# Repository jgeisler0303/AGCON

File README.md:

# This Project is no longer maintained. Please see if this might be an alternative for you: https://github.com/jgeisler0303/CANFestivino

Introduction
============
This project aims to provide hardware and software to build a versatile and generic device that can be used to connect all sorts of sensors and actuators to a CANopen network. My main intention is to use these devices in home automation applications.

Originally I wanted to cal the project CANduino but that name is already taken. Now I think that AGCON -- Arduino Generic CANopen Node -- is much more descriptive and unique.

The hardware is based on the ubiquitous ATmega 328 microcontroller found e.g. on the Arduino Uno. The mc is preflashed with the Arduino bootloader and can be programmed using an FTDI USB to serial adapter.

Connection to the CAN bus is established via an MCP2515 CAN controller.

The free input and output pins of the ATmega are not routed to the available connectors. Instead, the board features a prototyping area that can be used to customize the device to connect to any sensor or actuator. This allows to mass-produce the board and use it for many different applications.

The software is currently based on the http://www.canfestival.org/ CANopen stack adapted to run on the ATmega 328. For sending and receiving of CAN messages a modified version of the https://github.com/Seeed-Studio/CAN_BUS_Shield library is used. This example code is configured to let the user read 6 digital inputs and write 4 digital outputs. The software has to be compiled using the avr-gcc via a makefile.

The CANopen stack is a protocol that runs ontop of the CAN communication layer and facilitates the acces to device parameters and input/ouput data in a standardized way. Check out the following links to get a quick start on the basic concept:

* http://en.wikipedia.org/wiki/CANopen
* http://www.canopensolutions.com/english/about_canopen/about_canopen.shtml
* http://www.can-cia.org/index.php?id=503

In the future I plan to rewrite the software as an Arduino library so that the Arduino IDE can be used to configure the device behaviour, e.g. read special sensor protocols or to control pwm outputs.

Getting Started
===============
To compile the software, got to the Software/CanFestival/examples/Arduino subfolder and run ```make```. (This is assuming you have the avr-gcc compiler installed). If you have a USB to serial adapter connected to your PC and board you can also run ```make flash``` to directly download the new programm to your controller.
The software is not restricted to run on the supplied controller board. Though I haye not tested it, the software can be run on most Arduino boards with a CAN bus shield. But beware that in its current incarnation the SPI chip selection of the MCP2515 is not connected to PB2 (Arduino pin 10). If you want to use the software with CAN bus shields you will probably have to change the following line in mcp_can.c to match your chip select configuration:
```c
#define DDR_CS DDRD
#define PORT_CS PORTD
#define P_CS PD7
```

For the standard SS pin you will have to change these to
```c
#define DDR_CS DDRB
#define PORT_CS PORTB
#define P_CS PB2
```

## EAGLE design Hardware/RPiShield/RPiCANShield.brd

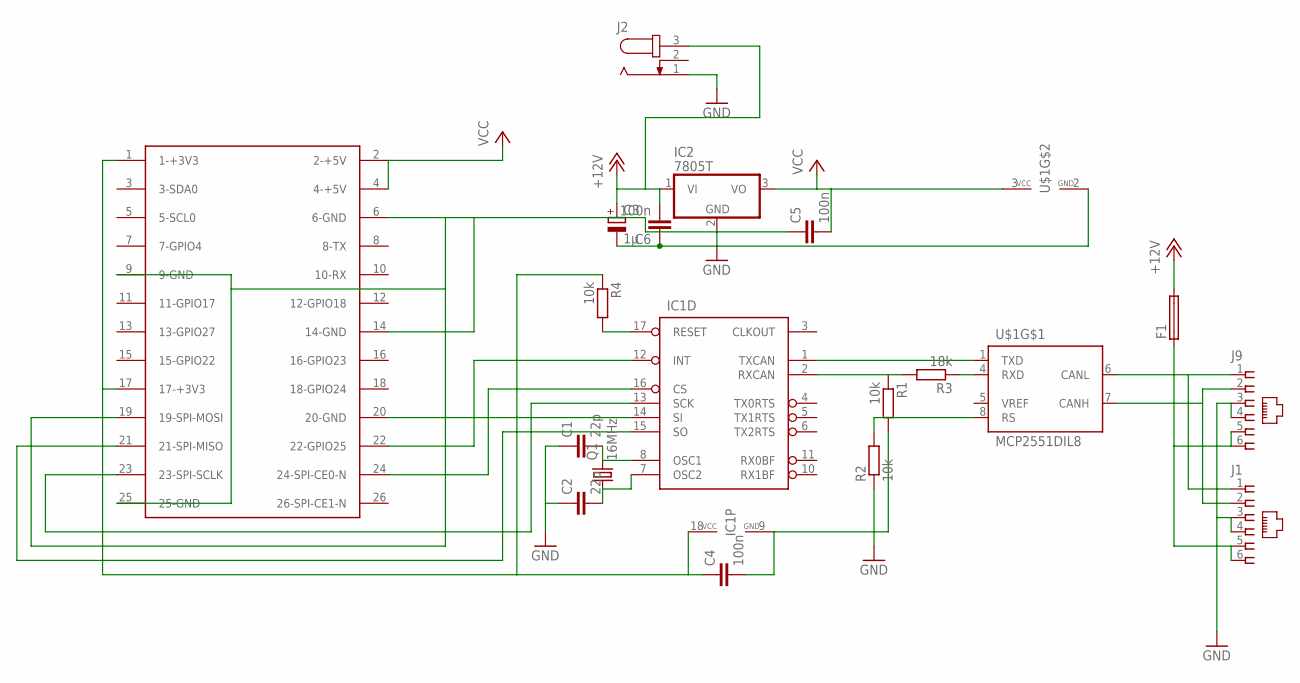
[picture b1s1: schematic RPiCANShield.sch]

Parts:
C1, C2: 22p; C025-024X044
C3: 1µ; E2-5
C4, C5, C6: 100n; C050-024X044
F1: PICOFUSE
IC1: MCP2515P; DIL18
IC2: 7805T; TO220H
J1, J9: 520250-3
J2: JACK-PLUG0; SPC4077
Q1: 16MHz; HC18U-V
R1, R2: 10k; 0207/7
R3: 18k; 0207/7
R4: 10k; 0204/5
U$1: MCP2551DIL8; DIL08
U$2: RASPBERRY-PI

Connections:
+12V: C3.+, C6.2, F1.2, IC2.1 (VI), J2.3
GND: C1.1, C2.1, C3.-, C4.2, C5.1, C6.1, IC1.9 (GND), IC2.2 (GND), J1.3, J1.4, J2.1, J9.3, J9.4, R1.2, R2.1, U$1.2 (GND), U$2.6 (6-GND), U$2.9 (9-GND), U$2.14 (14-GND), U$2.20 (20-GND), U$2.25 (25-GND)
unnamed: IC1.1 (TXCAN), U$1.1 (TXD)
unnamed: R3.1, U$1.4 (RXD)
unnamed: J1.1, J9.1, U$1.6 (CANL)
unnamed: J1.2, J9.2, U$1.7 (CANH)
unnamed: F1.1, J1.5, J1.6, J9.5, J9.6
unnamed: IC1.2 (RXCAN), R1.1, R3.2
unnamed: R2.2, U$1.8 (RS)
unnamed: C4.1, IC1.18 (VCC), R4.1, U$2.1 (1-+3V3), U$2.17 (17-+3V3)
unnamed: IC1.17 (RESET), R4.2
unnamed: IC1.16 (CS), U$2.24 (24-SPI-CE0-N)
unnamed: IC1.13 (SCK), U$2.23 (23-SPI-SCLK)
unnamed: IC1.14 (SI), U$2.19 (19-SPI-MOSI)
unnamed: IC1.12 (INT), U$2.22 (22-GPIO25)
unnamed: IC1.15 (SO), U$2.21 (21-SPI-MISO)
unnamed: C1.2, IC1.8 (OSC1), Q1.2
unnamed: C2.2, IC1.7 (OSC2), Q1.1
VCC: C5.2, IC2.3 (VO), U$1.3 (VCC), U$2.2 (2-+5V), U$2.4 (4-+5V)

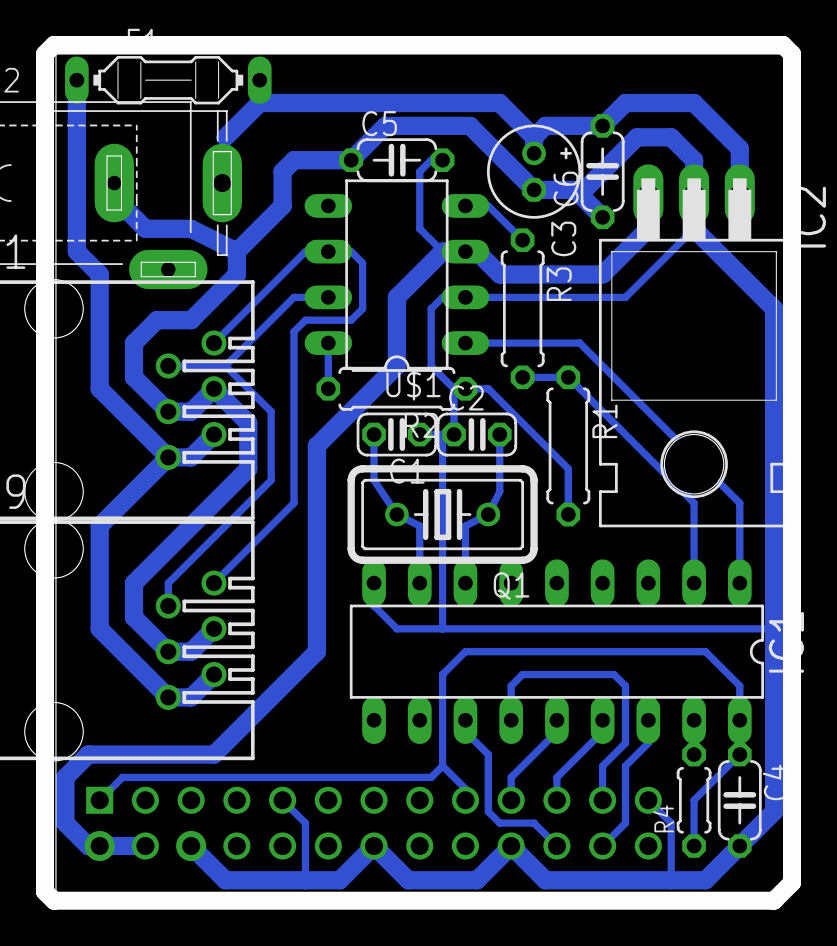
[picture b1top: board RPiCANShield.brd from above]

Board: 2 copper layers, 41.5 x 47.5 mm, 19 parts (1 on the bottom side), 19 nets.

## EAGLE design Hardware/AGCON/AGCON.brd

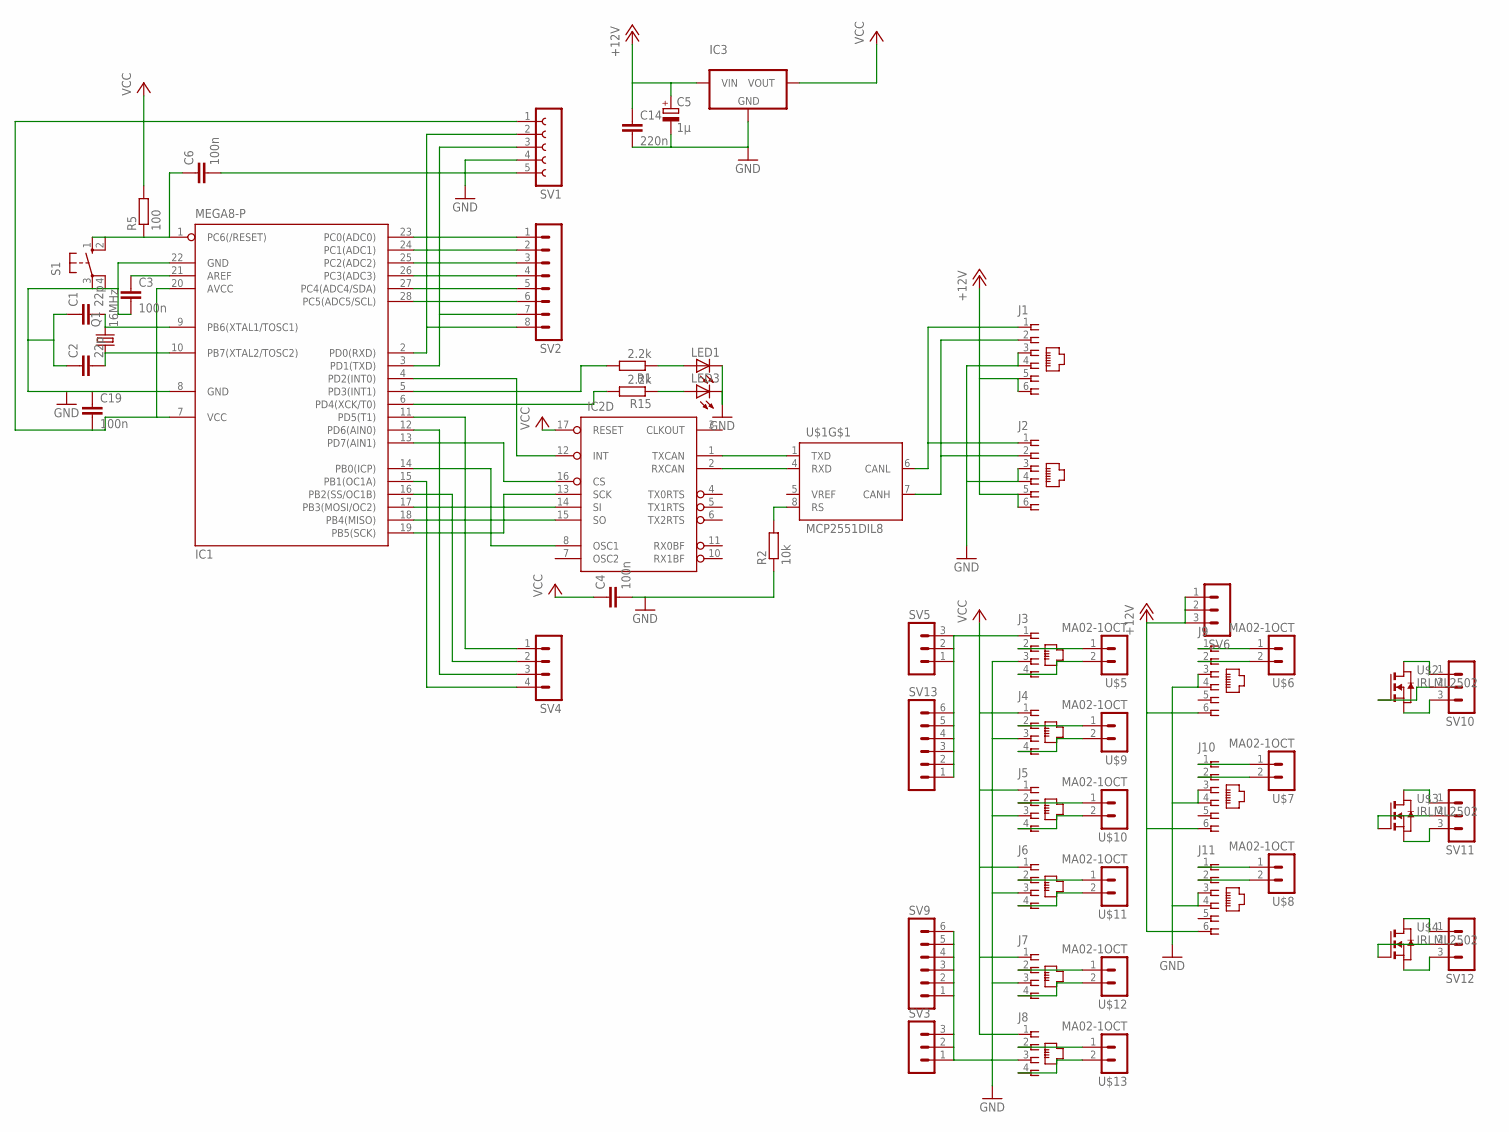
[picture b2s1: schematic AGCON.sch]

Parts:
C1, C2: 22p; C025-024X044
C3, C4, C6, C19: 100n; C050-024X044
C5: 1µ; E5-10,5
C14: 220n; C050-024X044
IC1: MEGA8-P; DIL28-3
IC2: MCP2515P; DIL18
IC3: MCP1702; TO-92
J1, J2, J9, J10, J11: 520250-3
J3, J4, J5, J6, J7, J8: 520249-2
LED1, LED3: LED3MM
Q1: 16MHz; HC18U-V
R1, R15: 2.2k; 0207/7
R2: 10k; 0207/7
R5: 100; 0207/7
S1: 10-XX; B3F-10XX
SV1: FE05-1
SV2: MA08-1OCT
SV3, SV5, SV6, SV10, SV11, SV12: MA03-1OCT
SV4: MA04-1OCT
SV9, SV13: MA06-1MA06-1OCT; MA06-1OCT
U$1: MCP2551DIL8; DIL08
U$2, U$3, U$4: IRLML2502; SOT-23
U$5, U$6, U$7, U$8, U$9, U$10, U$11, U$12, U$13: MA02-1OCT

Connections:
+12V: C5.+, C14.1, IC3.2 (VIN), J1.5, J1.6, J2.5, J2.6, J9.6, J10.6, J11.6, SV6.1, SV6.2, SV6.3
GND: C1.1, C2.1, C3.2, C4.2, C5.-, C14.2, C19.1, IC1.8 (GND), IC1.22 (GND), IC2.9 (GND), IC3.1 (GND), J1.3, J1.4, J2.3, J2.4, J3.3, J4.3, J5.3, J6.3, J7.3, J8.3, J9.3, J9.4, J10.3, J10.4, J11.3, J11.4, LED1.K (C), LED3.K (C), R2.1, S1.3, S1.4 (P1), SV1.4, SV3.1, SV3.2, SV3.3, SV9.1, SV9.2, SV9.3, SV9.4, SV9.5, SV9.6, U$1.2 (GND)
unnamed: IC1.18 (PB4(MISO)), IC2.15 (SO)
unnamed: IC1.17 (PB3(MOSI/OC2)), IC2.14 (SI)
unnamed: IC1.19 (PB5(SCK)), IC2.13 (SCK)
unnamed: IC2.1 (TXCAN), U$1.1 (TXD)
unnamed: IC2.2 (RXCAN), U$1.4 (RXD)
unnamed: J1.1, J2.1, U$1.6 (CANL)
unnamed: J1.2, J2.2, U$1.7 (CANH)
unnamed: IC1.6 (PD4(XCK/T0)), R15.2
unnamed: C6.1, IC1.1 (PC6(/RESET)), R5.1, S1.1 (S), S1.2 (S1)
unnamed: LED1.A, R1.1
unnamed: C6.2, SV1.5
unnamed: LED3.A, R15.1
unnamed: IC1.5 (PD3(INT1)), R1.2
unnamed: IC1.14 (PB0(ICP)), IC2.8 (OSC1)
unnamed: R2.2, U$1.8 (RS)
unnamed: IC1.3 (PD1(TXD)), SV1.3, SV2.7
unnamed: IC1.2 (PD0(RXD)), SV1.2, SV2.8
unnamed: IC1.4 (PD2(INT0)), IC2.12 (INT)
unnamed: IC1.13 (PD7(AIN1)), IC2.16 (CS)
unnamed: C3.1, IC1.21 (AREF)
unnamed: IC1.23 (PC0(ADC0)), SV2.1
unnamed: C1.2, IC1.9 (PB6(XTAL1/TOSC1)), Q1.2
unnamed: C2.2, IC1.10 (PB7(XTAL2/TOSC2)), Q1.1
unnamed: IC1.24 (PC1(ADC1)), SV2.2
unnamed: IC1.25 (PC2(ADC2)), SV2.3
unnamed: IC1.26 (PC3(ADC3)), SV2.4
unnamed: IC1.27 (PC4(ADC4/SDA)), SV2.5
unnamed: IC1.28 (PC5(ADC5/SCL)), SV2.6
unnamed: J4.2, U$9.1
unnamed: J5.2, U$10.1
unnamed: IC1.11 (PD5(T1)), SV4.1
unnamed: IC1.12 (PD6(AIN0)), SV4.3
unnamed: IC1.15 (PB1(OC1A)), SV4.4
unnamed: IC1.16 (PB2(SS/OC1B)), SV4.2
unnamed: J6.2, U$11.1
unnamed: J9.1, U$6.1
unnamed: J9.2, U$6.2
unnamed: J10.1, U$7.1
unnamed: J3.2, U$5.1
unnamed: J3.4, U$5.2
unnamed: J10.2, U$7.2
unnamed: J4.4, U$9.2
unnamed: J11.1, U$8.1
unnamed: J5.4, U$10.2
unnamed: J11.2, U$8.2
unnamed: J6.4, U$11.2
unnamed: J7.2, U$12.1
unnamed: J7.4, U$12.2
unnamed: J8.2, U$13.1
unnamed: J8.4, U$13.2
unnamed: SV10.1, U$2.3 (D)
unnamed: SV10.2, U$2.1 (G)
unnamed: SV10.3, U$2.2 (S)
unnamed: SV11.1, U$3.3 (D)
unnamed: SV11.2, U$3.1 (G)
unnamed: SV11.3, U$3.2 (S)
unnamed: SV12.1, U$4.3 (D)
unnamed: SV12.2, U$4.1 (G)
unnamed: SV12.3, U$4.2 (S)
VCC: C4.1, C19.2, IC1.7 (VCC), IC1.20 (AVCC), IC2.17 (RESET), IC2.18 (VCC), IC3.3 (VOUT), J3.1, J4.1, J5.1, J6.1, J7.1, J8.1, R5.2, SV1.1, SV5.1, SV5.2, SV5.3, SV13.1, SV13.2, SV13.3, SV13.4, SV13.5, SV13.6, U$1.3 (VCC)

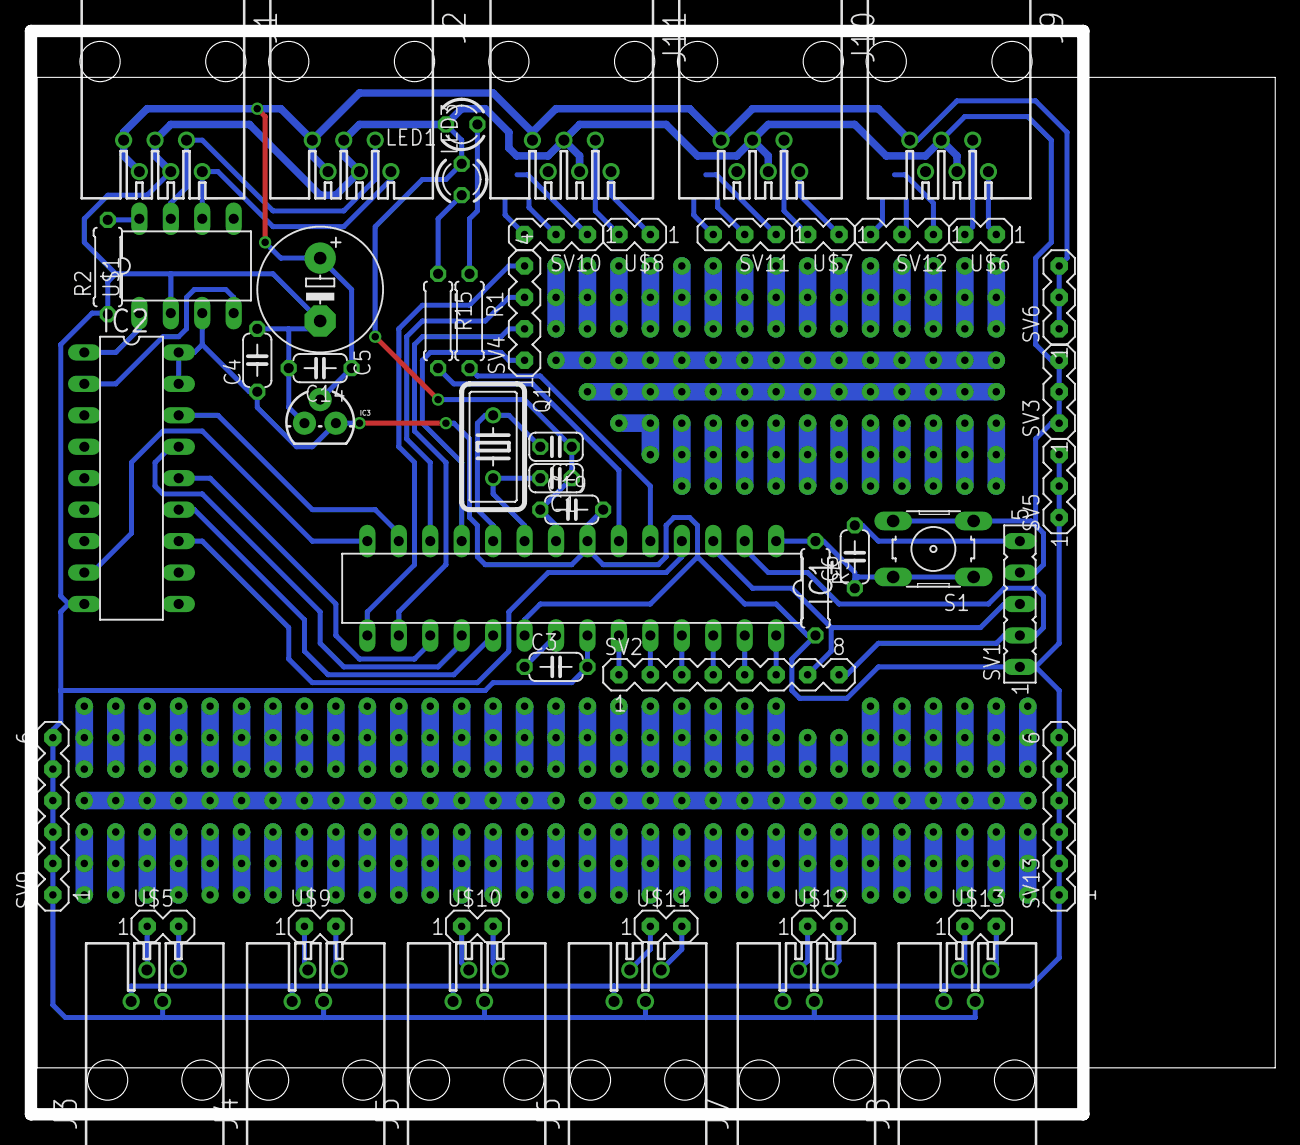
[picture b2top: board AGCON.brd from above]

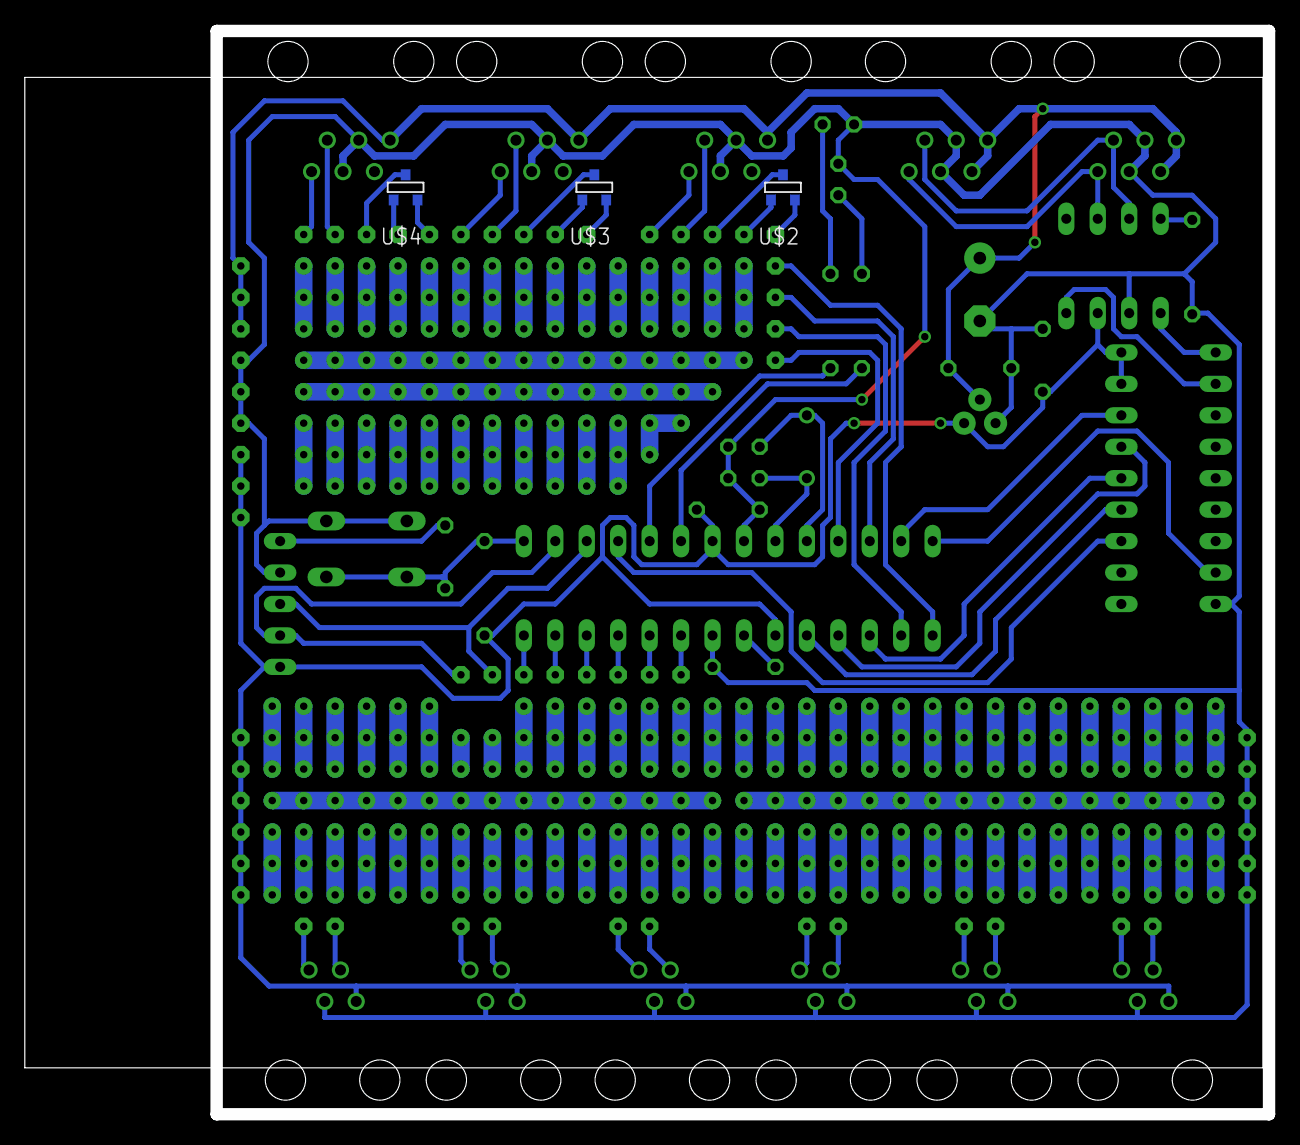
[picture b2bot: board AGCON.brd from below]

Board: 2 copper layers, 100.5 x 87.5 mm, 54 parts (3 on the bottom side), 62 nets.

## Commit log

2014-12-12 initial commit of CanFestival from 12 Jun 2014, hash 7740ac6fdedc
2014-12-12 initial commit of Arduino plus MCP2515 implementation
2014-12-12 added Eagle files of single layer AGCON board
2014-12-18 started Arduino library project. Copy of example/Arduino compiles as cpp. New Makefile
2015-02-04 compiles with arduino libs
2015-02-04 added Raspberry Pi CAN bus shield
2015-02-11 changed generation of OD files to use explicit CANopen names for type id constants
2015-03-27 enabled input of node id in dialogs of objdictedit
2015-03-31 added first working CANopenSlave.ino
2015-03-31 removed wrong comment
